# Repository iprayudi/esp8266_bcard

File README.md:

# esp8266_bcard
Business card project using esp8266 module

This work is inspired by: https://www.thirtythreeforty.net/posts/2019/12/my-business-card-runs-linux/

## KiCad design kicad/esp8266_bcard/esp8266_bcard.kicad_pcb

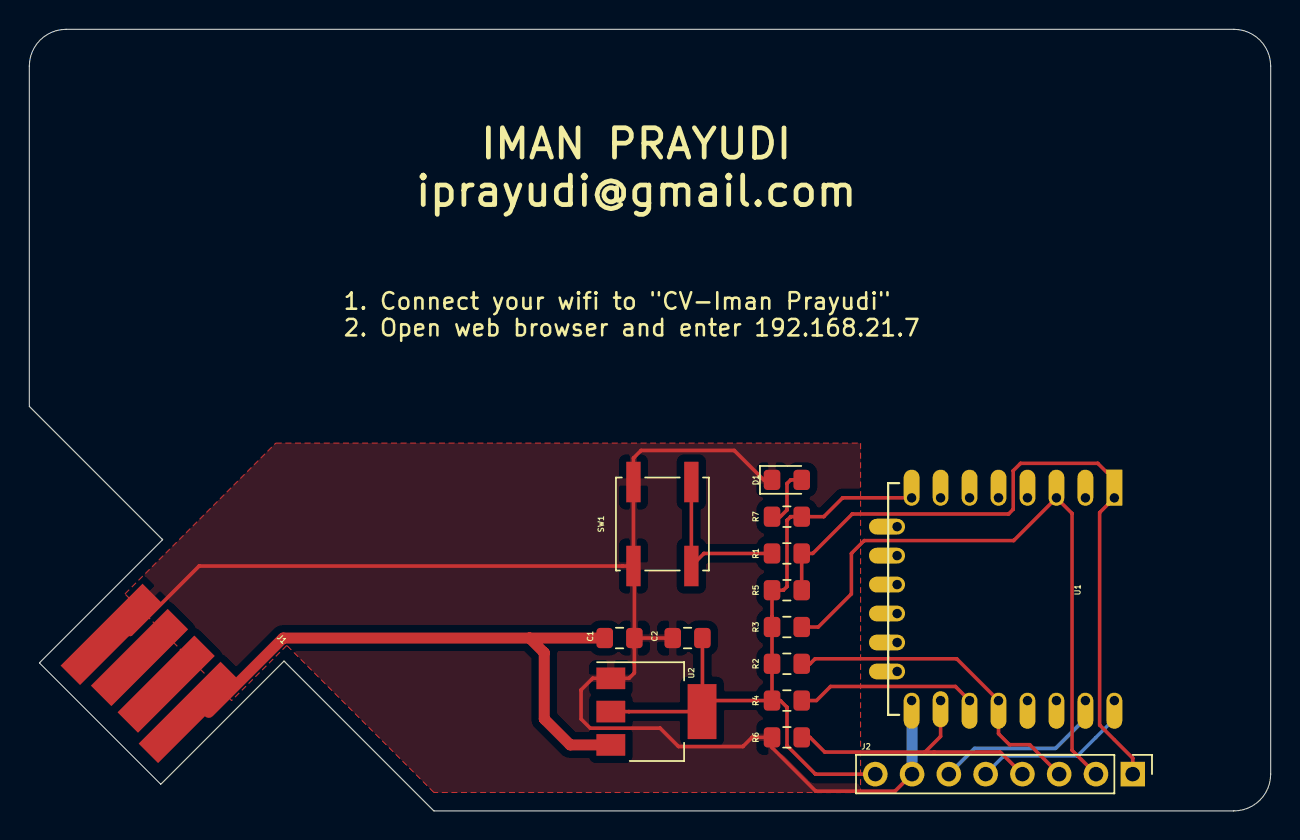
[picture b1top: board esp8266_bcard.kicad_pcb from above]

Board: 2 copper layers, 85.7 x 54.0 mm, 15 parts (0 on the bottom side), 12 nets.

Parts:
C1, C2: 10uF 25V; C_0805_2012Metric_Pad1.15x1.40mm_HandSolder
D1: LED; LED_0805_2012Metric_Pad1.15x1.40mm_HandSolder
J1: USB-A_PCB-Traces; CONN-USB-A-PCB-TRACES
J2: Prog_conn; PinHeader_1x08_P2.54mm_Vertical
R1, R7: 470; R_0805_2012Metric_Pad1.15x1.40mm_HandSolder
R2, R3, R4, R5, R6: 10K; R_0805_2012Metric_Pad1.15x1.40mm_HandSolder
SW1: SW_Push; SW_Push_1P1T_NO_CK_KSC7xxJ
U1: ESP-12F; ESP-12E
U2: NCP1117ST33T3G; SOT-223-3_TabPin2

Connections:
/3.3V: C2.1, J2.8, R2.2, R3.2, R4.2, R5.2, R7.1, U1.8, U2.2
/EN: J2.2, R3.1, U1.3
/GND: C1.2, C2.2, D1.1, J1.4, J2.7, R6.2, SW1.2, U1.9, U2.1
/GPIO0: J2.3, R2.1, U1.12
/GPIO2: R4.1, U1.11
/GPIO15: J2.4, R6.1, U1.10
/RX: J2.6, U1.15
/TX: J2.5, U1.16
/VUSB: C1.1, J1.1, U2.3
/nRST: J2.1, R1.1, R5.1, U1.1
unnamed: D1.2, R7.2
unnamed: R1.2, SW1.1

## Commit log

2019-12-29 schematic updated
2019-12-30 minor updates
2020-01-15 added example code
